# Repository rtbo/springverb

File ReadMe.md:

# Spring 'Verb

## Spring Tank

From my Fender Deluxe 112 amp
Accutronics model 8 E B2 C 1 B

- 3 springs model
- input
  - impedance @1kHz 800 ohms
  - inductance 150 mH
  - DC resistance 75 ohms
  - drive current 3.1 mA
- output
  - impedance @1kHz 2575 ohms
  - inductance 400 mH
  - DC resistance 230 ohms
  - decay time 1.75 to 3 seconds

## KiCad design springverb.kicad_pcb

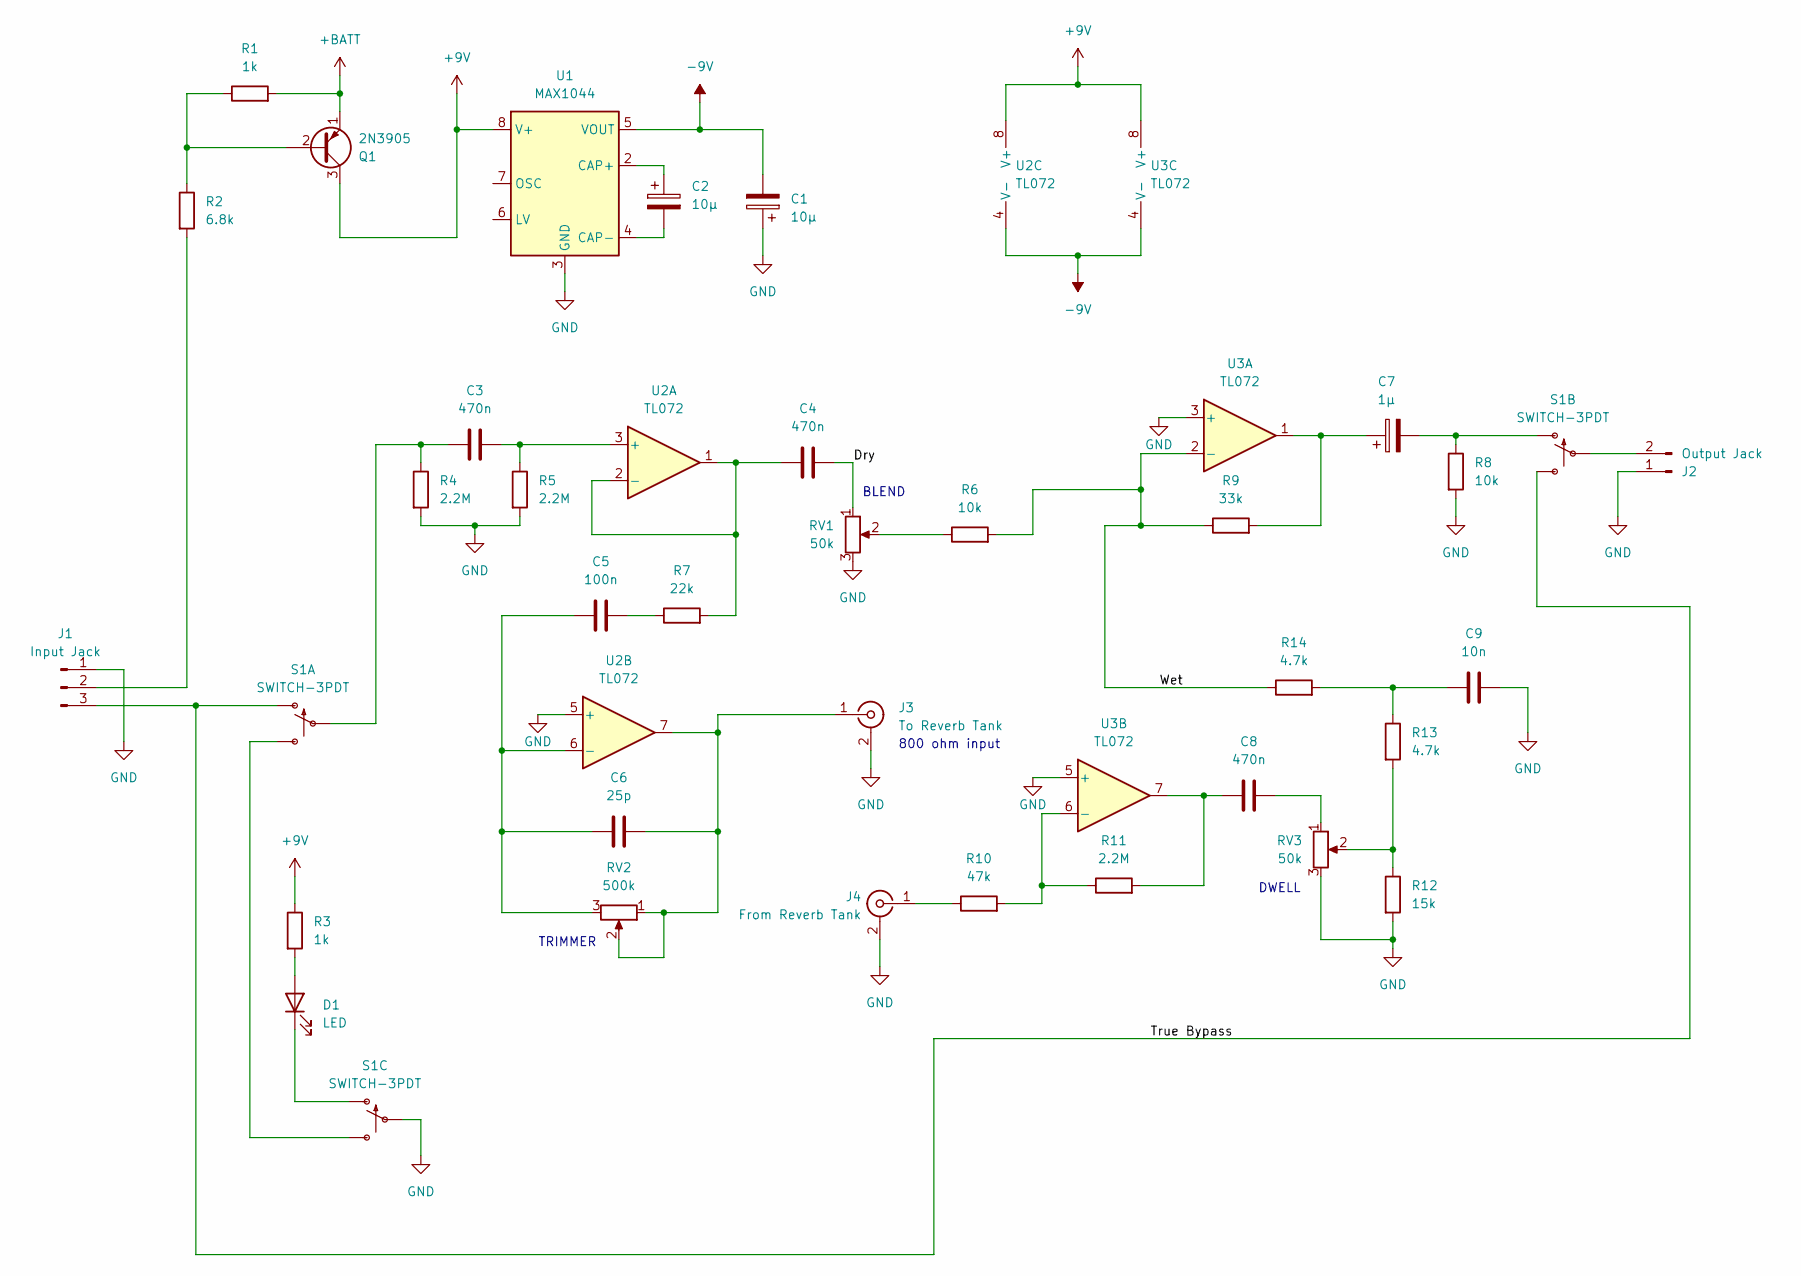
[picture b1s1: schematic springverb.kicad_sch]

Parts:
C1, C2: 10µ; CP_Radial_D5.0mm_P2.00mm
C3, C4: 470n; C_Rect_L7.0mm_W2.0mm_P5.00mm
C5: 100n; C_Rect_L7.0mm_W2.0mm_P5.00mm
C6: 25p; C_Disc_D3.0mm_W2.0mm_P2.50mm
C7: 1µ; CP_Radial_D5.0mm_P2.00mm
C8: 470n; C_Rect_L7.0mm_W2.5mm_P5.00mm
C9: 10n; C_Rect_L7.0mm_W2.5mm_P5.00mm
D1: LED; PinHeader_1x02_P2.54mm_Vertical
J1: Input Jack; PinHeader_1x03_P2.54mm_Vertical
J2: Output Jack; PinHeader_1x02_P2.54mm_Vertical
J3: To Reverb Tank; PinHeader_1x02_P2.54mm_Vertical
J4: From Reverb Tank; PinHeader_1x02_P2.54mm_Vertical
Q1: 2N3905; TO-92_Inline
R1, R3: 1k; R_Axial_DIN0207_L6.3mm_D2.5mm_P2.54mm_Vertical
R2: 6.8k; R_Axial_DIN0207_L6.3mm_D2.5mm_P2.54mm_Vertical
R4, R5, R11: 2.2M; R_Axial_DIN0207_L6.3mm_D2.5mm_P2.54mm_Vertical
R6, R8: 10k; R_Axial_DIN0207_L6.3mm_D2.5mm_P2.54mm_Vertical
R7: 22k; R_Axial_DIN0207_L6.3mm_D2.5mm_P2.54mm_Vertical
R9: 33k; R_Axial_DIN0207_L6.3mm_D2.5mm_P2.54mm_Vertical
R10: 47k; R_Axial_DIN0207_L6.3mm_D2.5mm_P2.54mm_Vertical
R12: 15k; R_Axial_DIN0207_L6.3mm_D2.5mm_P2.54mm_Vertical
R13, R14: 4.7k; R_Axial_DIN0207_L6.3mm_D2.5mm_P2.54mm_Vertical
RV1, RV3: 50k; PinHeader_1x03_P2.54mm_Vertical
RV2: 500k; Potentiometer_Bourns_3266W_Vertical
S1: SWITCH-3PDT; STOMP-SWITCH-3PDT
U1: MAX1044; DIP-8_W7.62mm
U2, U3: TL072; DIP-8_W7.62mm

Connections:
+9V: Q1.3 (C), R3.1, U1.8 (V+), U2.8 (V+), U3.8 (V+)
+BATT: Q1.1 (E), R1.2
-9V: C1.2, U1.5 (VOUT), U2.4 (V-), U3.4 (V-)
/Dry: C4.2, RV1.1
/True Bypass: J1.3, S1.P$1 (O), S1.P$6 (S)
/Wet: R6.2, R9.1, R14.1, U3.2 (-)
GND: C1.1, C9.2, J1.1, J2.1, J3.2 (Ext), J4.2 (Ext), R4.2, R5.2, R8.2, R12.2, RV1.3, RV3.3, S1.P$8, U1.3 (GND), U2.5 (+), U3.3 (+), U3.5 (+)
unnamed: C5.2, R7.1
unnamed: C7.1, R9.2, U3.1
unnamed: C8.1, R11.2, U3.7
unnamed: C8.2, RV3.1
unnamed: C9.1, R13.1, R14.2
unnamed: D1.2 (A), R3.2
unnamed: D1.1 (K), S1.P$7 (O)
unnamed: J1.2, R2.2
unnamed: J2.2, S1.P$5
unnamed: C6.2, J3.1 (In), RV2.1, RV2.2, U2.7
unnamed: J4.1 (In), R10.1
unnamed: Q1.2 (B), R1.1, R2.1
unnamed: R6.1, RV1.2
unnamed: R12.1, R13.2, RV3.2
unnamed: C3.1, R4.1, S1.P$2
unnamed: S1.P$3 (S), S1.P$9 (S)
unnamed: C7.2, R8.1, S1.P$4 (O)
unnamed: C2.1, U1.2 (CAP+)
unnamed: C2.2, U1.4 (CAP-)
unnamed: C3.2, R5.1, U2.3 (+)
unnamed: C4.1, R7.2, U2.1, U2.2 (-)
unnamed: C5.1, C6.1, RV2.3, U2.6 (-)
unnamed: R10.2, R11.1, U3.6 (-)

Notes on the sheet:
BLEND
TRIMMER
800 ohm input
DWELL

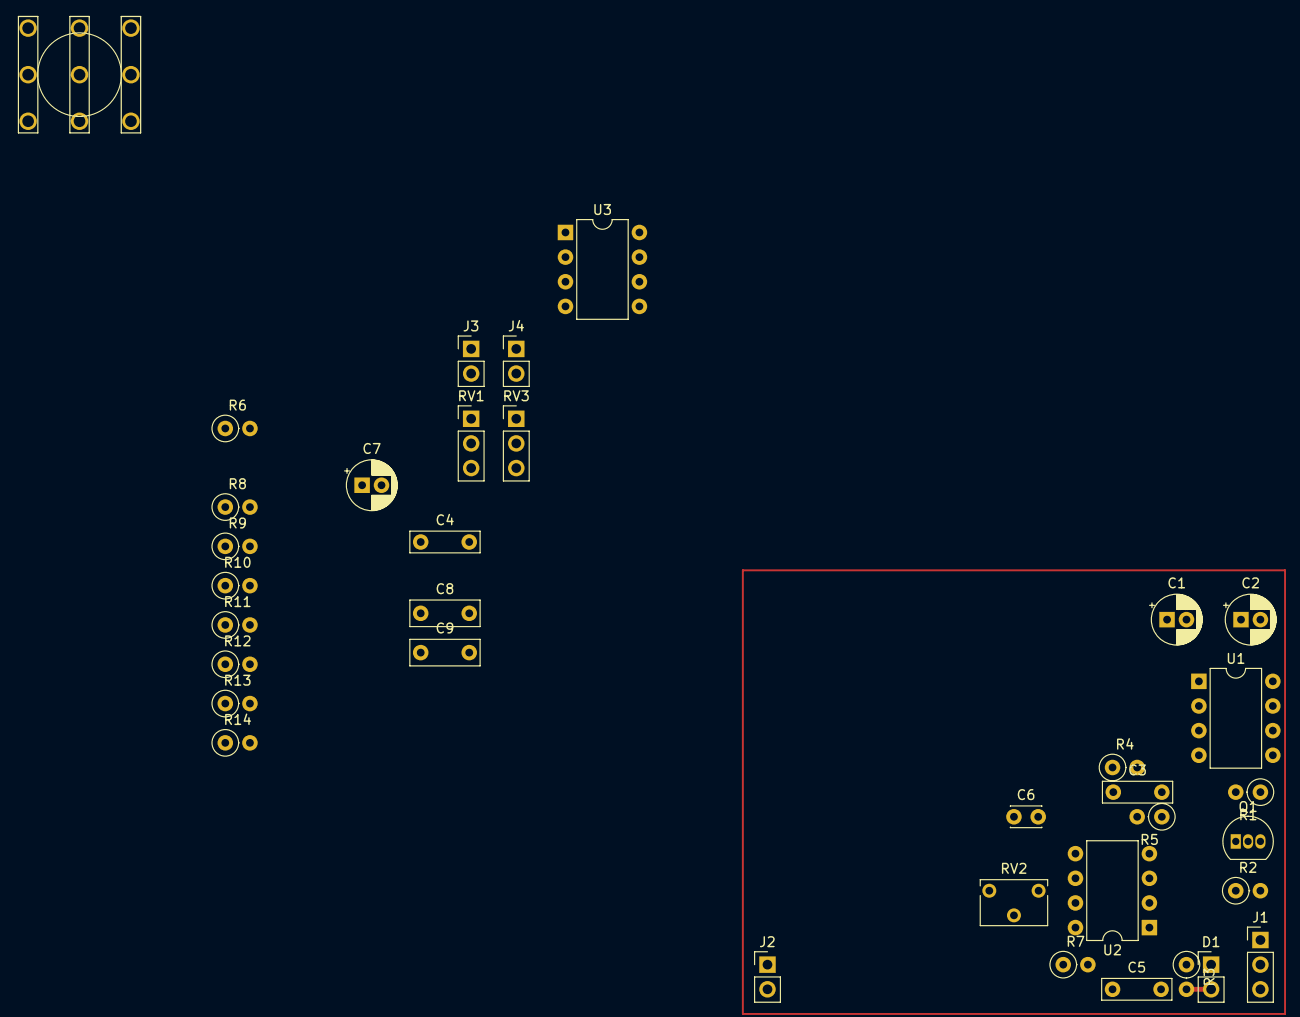
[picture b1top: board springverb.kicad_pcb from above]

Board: 2 copper layers, 36 parts (0 on the bottom side), 30 nets.

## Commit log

2024-09-13 initial import
